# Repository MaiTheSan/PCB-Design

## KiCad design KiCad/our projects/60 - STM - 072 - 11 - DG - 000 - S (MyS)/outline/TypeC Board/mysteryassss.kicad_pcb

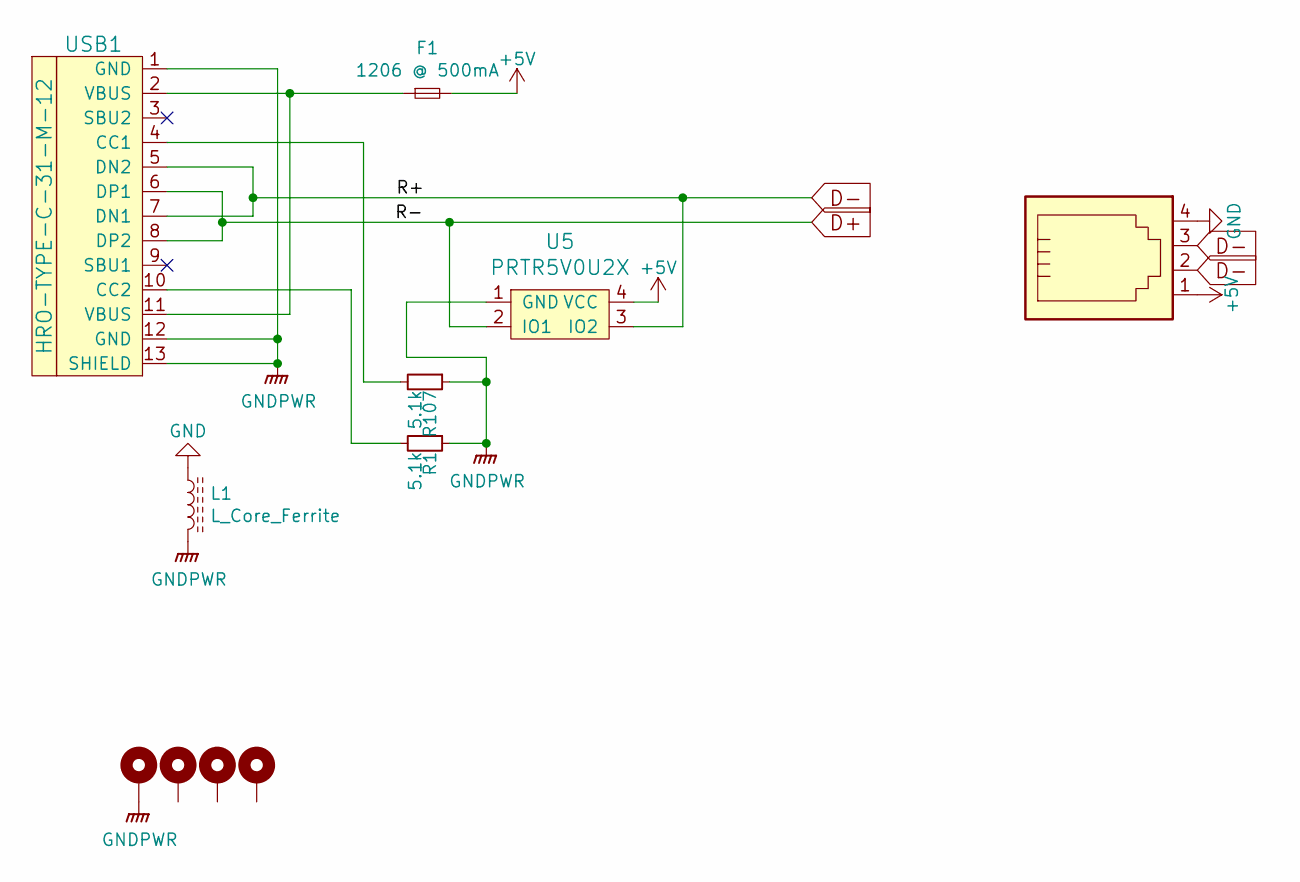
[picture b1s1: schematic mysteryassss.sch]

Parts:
CASE2, CASE3, CASE4, CASE5: ESD inrush; MountingHole_2.2mm_M2_Pad_Via
F1: 1206 @ 500mA; Fuse_1206_3216Metric
J2: 4P4C; JST_SH_SM04B-SRSS-TB_1x04-1MP_P1.00mm_Horizontal
L1: L_Core_Ferrite; L_1206_3216Metric
R1, R107: 5.1k; R_0603
U5: PRTR5V0U2X; SOT143B
USB1: HRO-TYPE-C-31-M-12; HRO-TYPE-C-31-M-12-Assembly

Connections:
+5V: F1.2, J2.1, U5.4 (VCC)
D+: U5.2 (IO1), USB1.6 (DP1), USB1.8 (DP2)
D-: J2.2, J2.3, U5.3 (IO2), USB1.5 (DN2), USB1.7 (DN1)
GND: J2.4, L1.1
GNDPWR: CASE2.1, L1.2, R1.1, R107.1, U5.1 (GND), USB1.1 (GND), USB1.12 (GND), USB1.13 (SHIELD)
unnamed: F1.1, USB1.2 (VBUS), USB1.11 (VBUS)
unnamed: R1.2, USB1.10 (CC2)
unnamed: R107.2, USB1.4 (CC1)

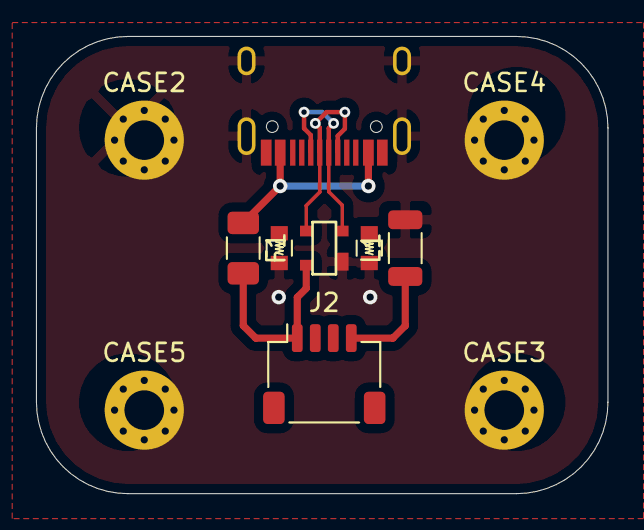
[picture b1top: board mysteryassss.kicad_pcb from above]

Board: 2 copper layers, 31.8 x 25.4 mm, 11 parts (0 on the bottom side), 8 nets.

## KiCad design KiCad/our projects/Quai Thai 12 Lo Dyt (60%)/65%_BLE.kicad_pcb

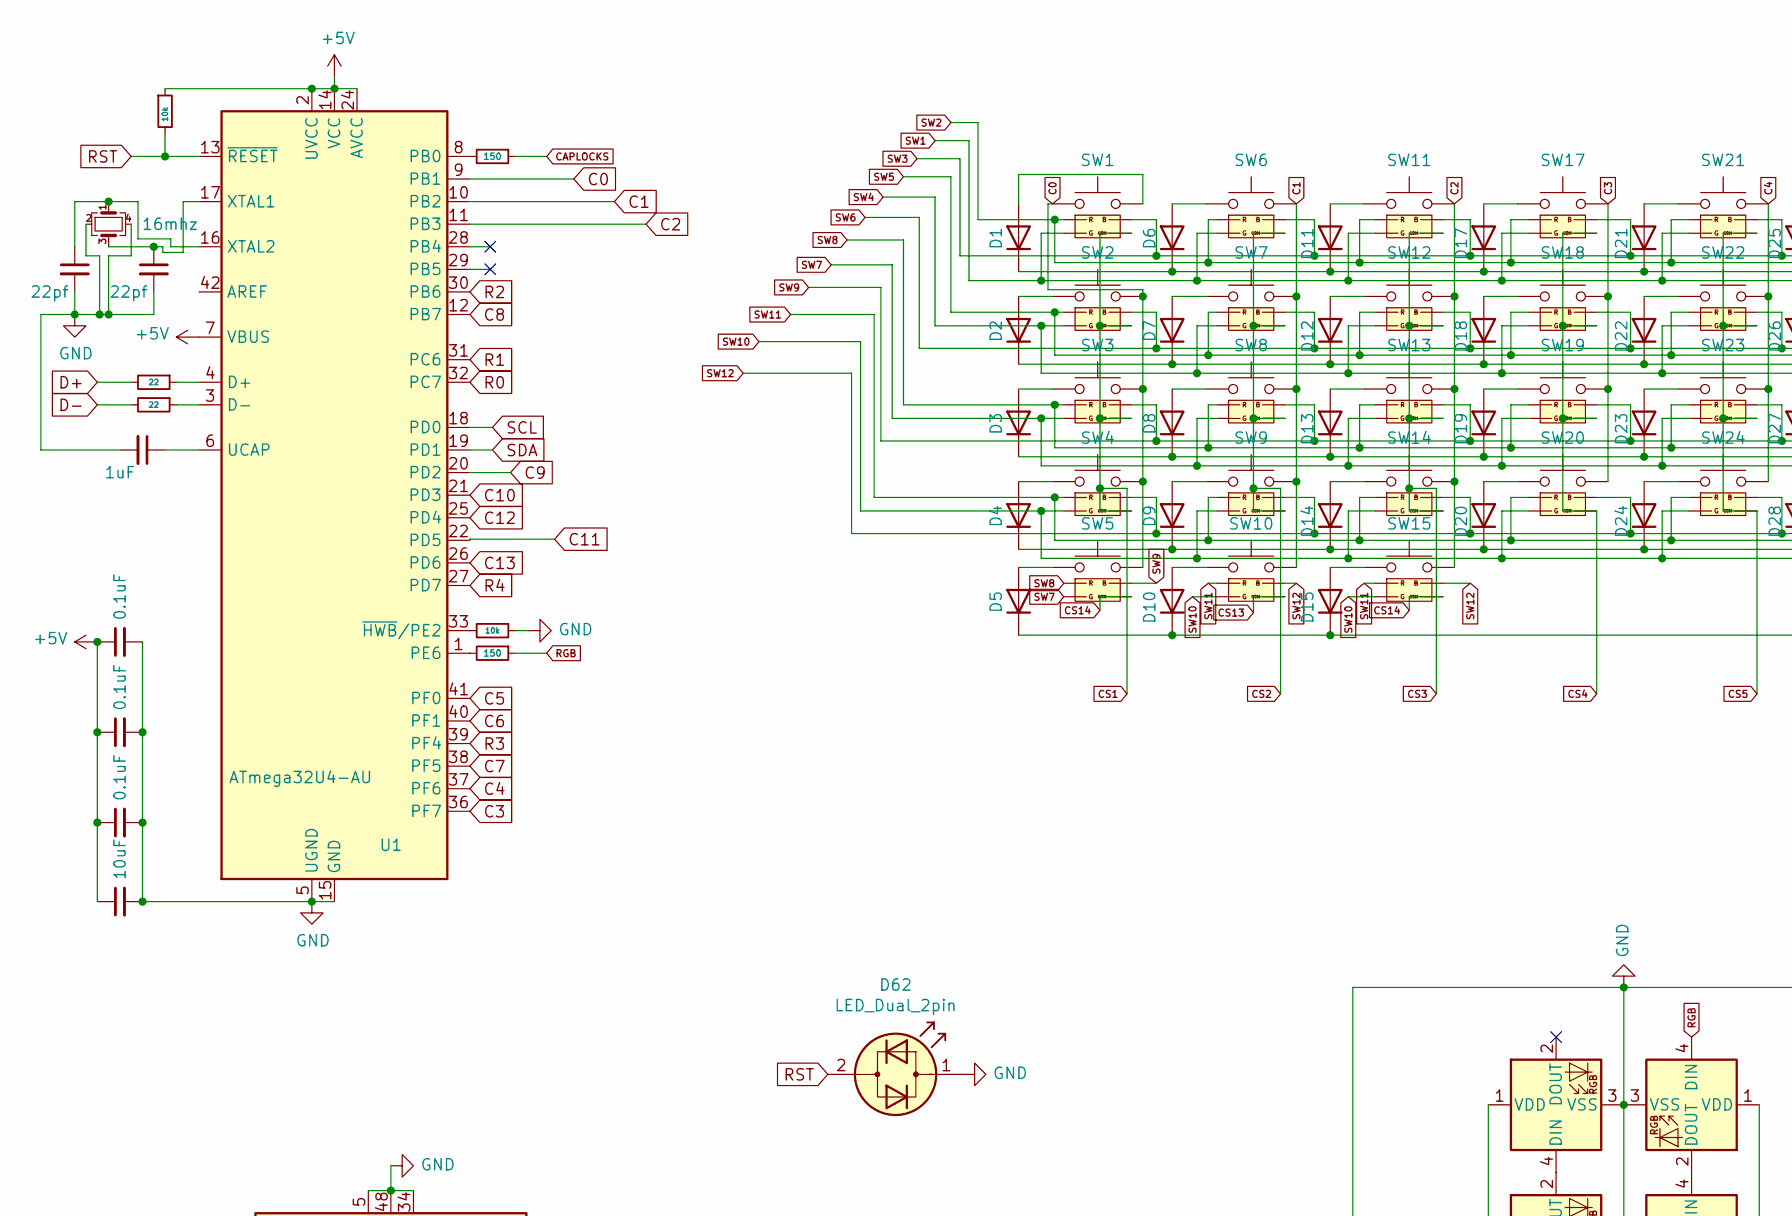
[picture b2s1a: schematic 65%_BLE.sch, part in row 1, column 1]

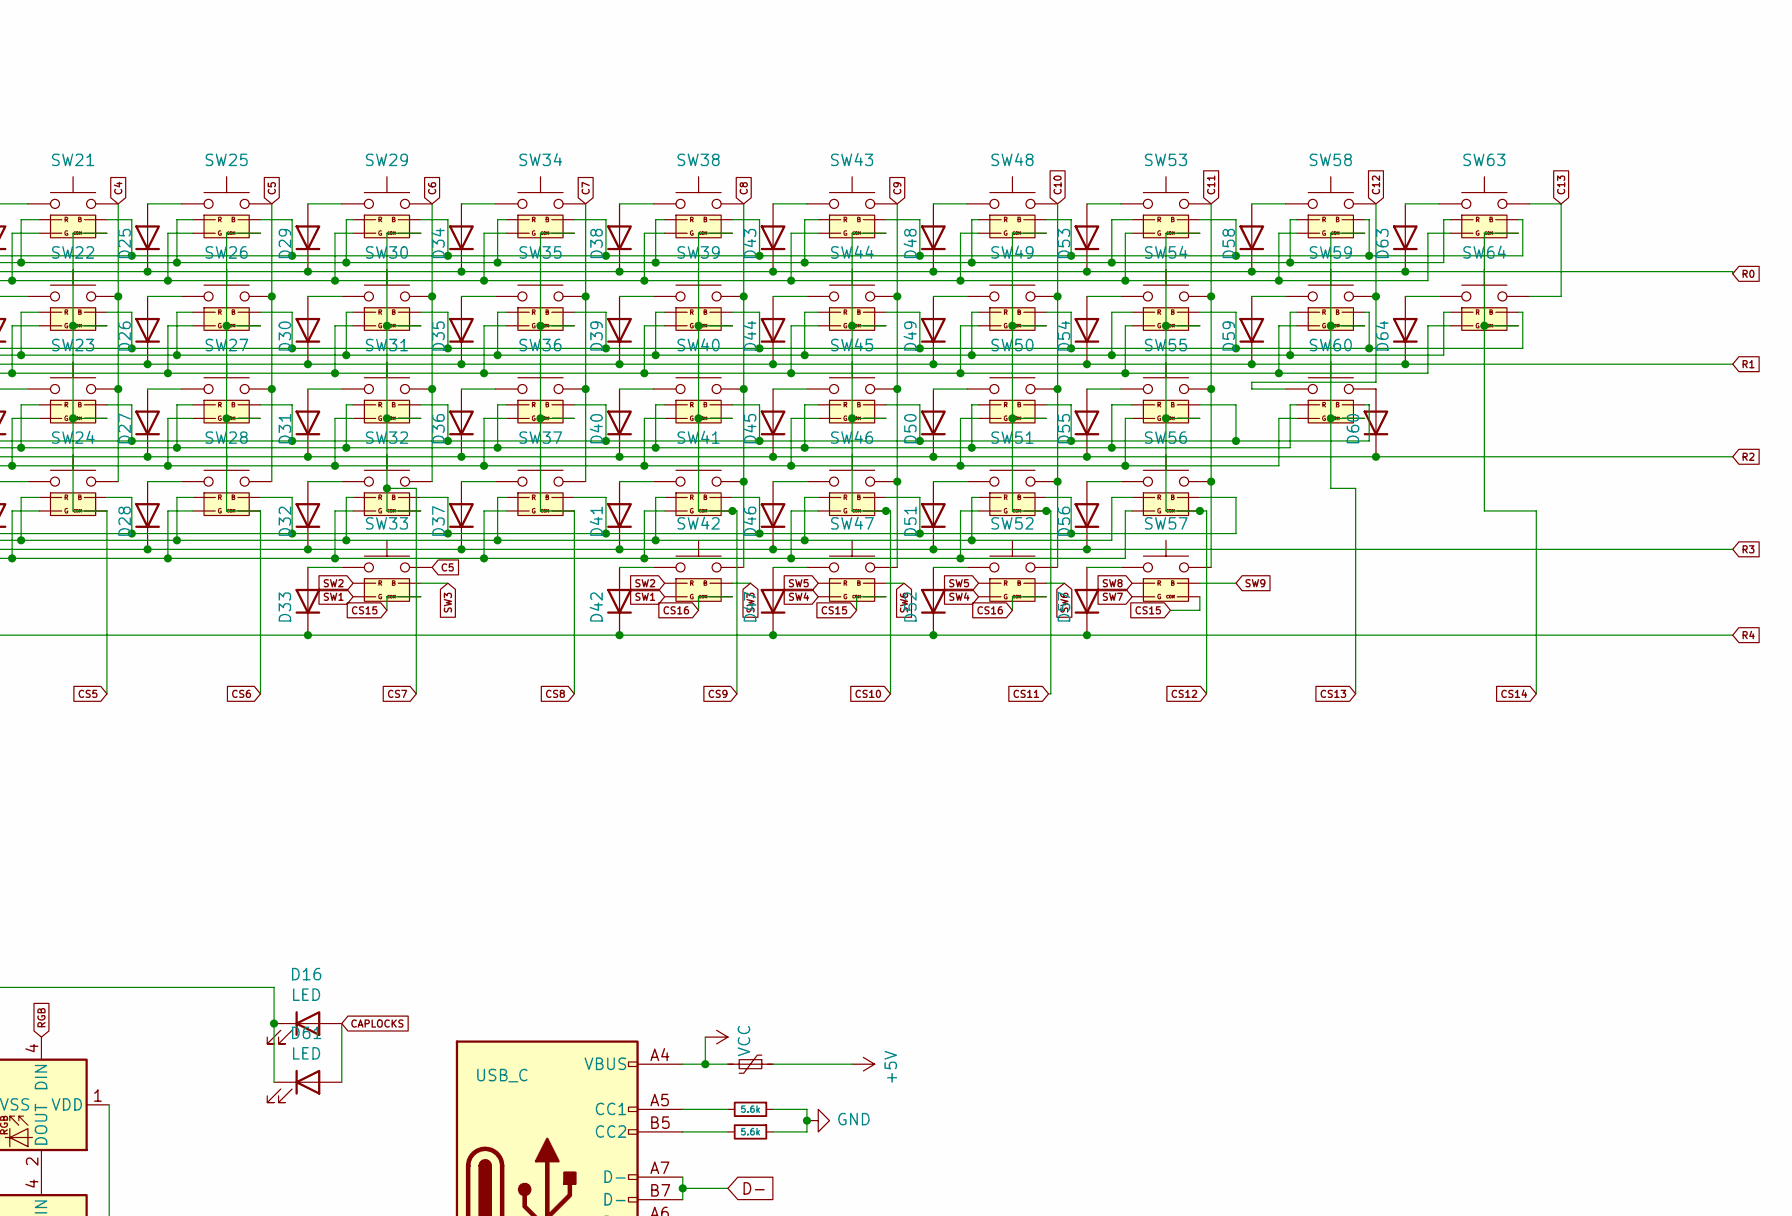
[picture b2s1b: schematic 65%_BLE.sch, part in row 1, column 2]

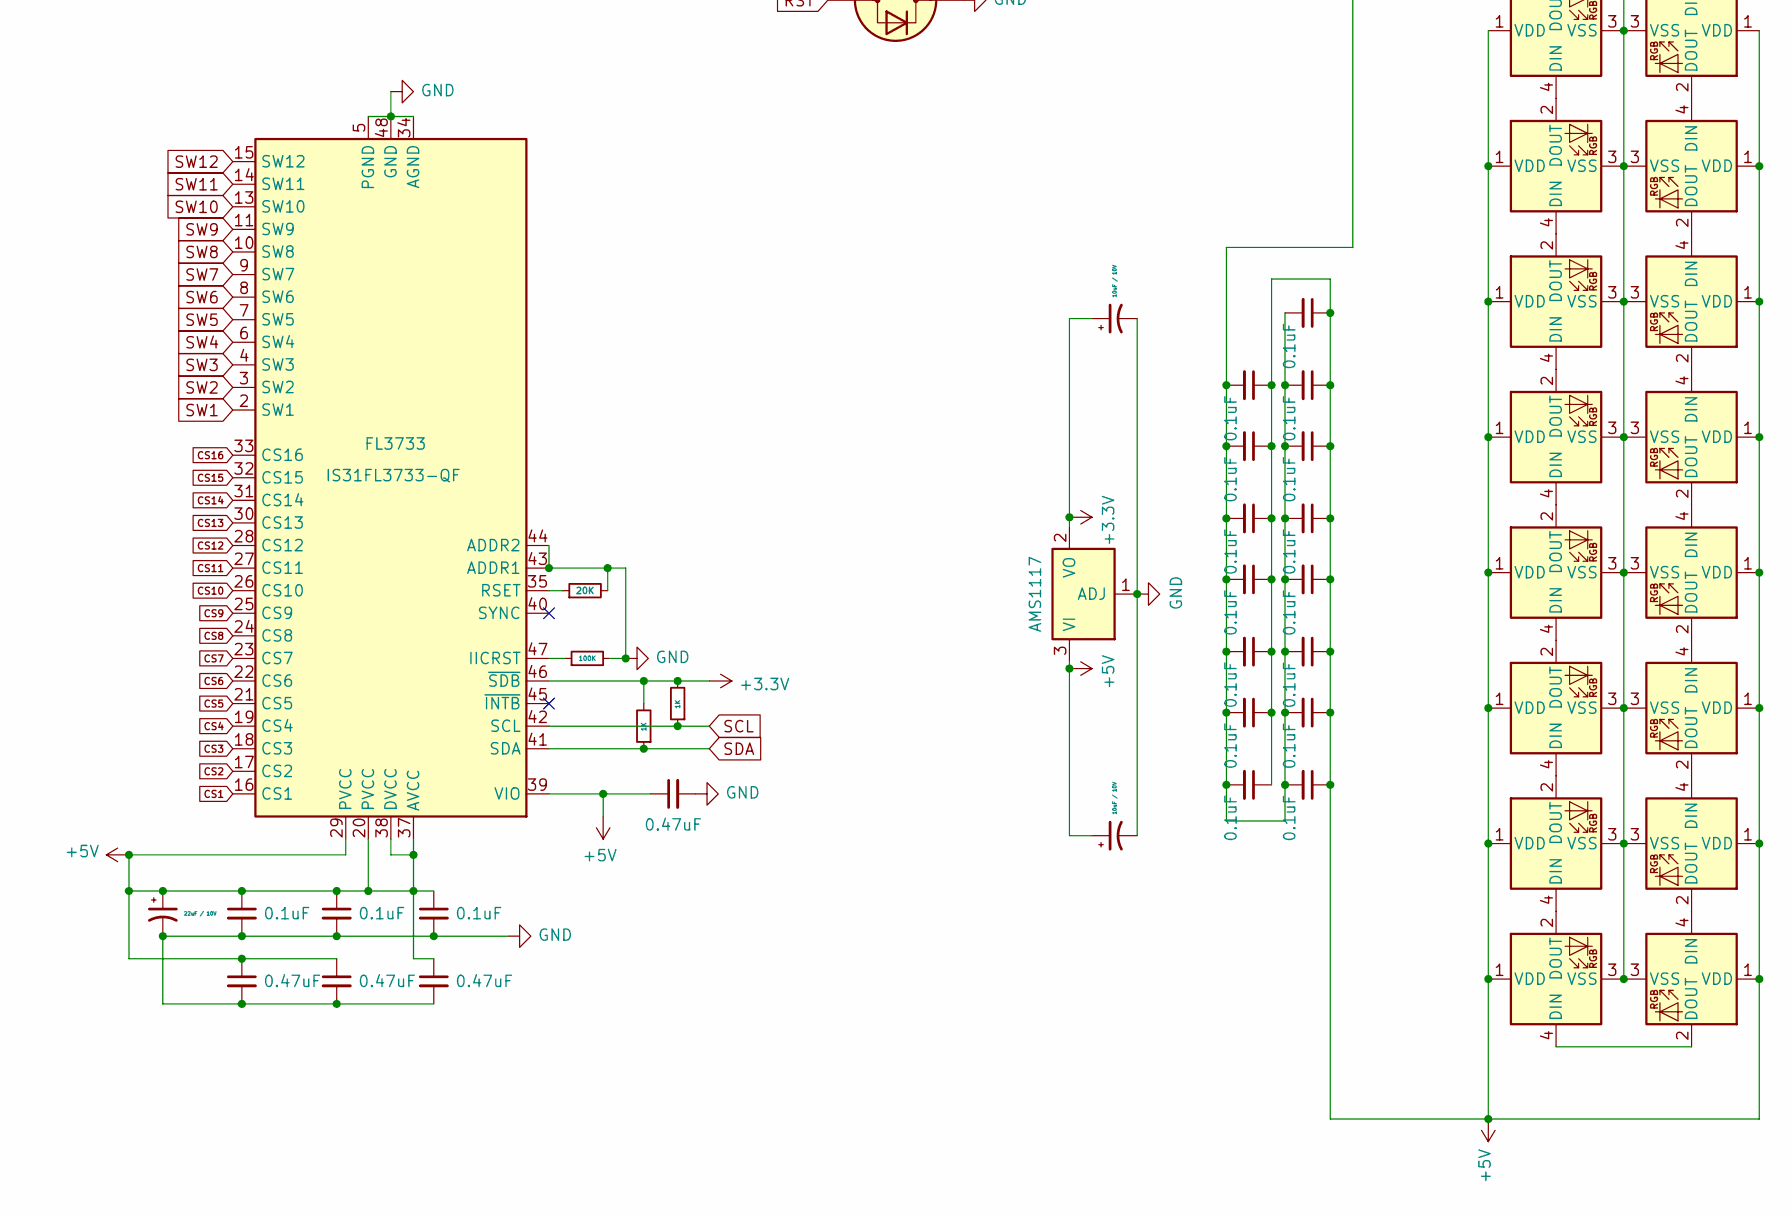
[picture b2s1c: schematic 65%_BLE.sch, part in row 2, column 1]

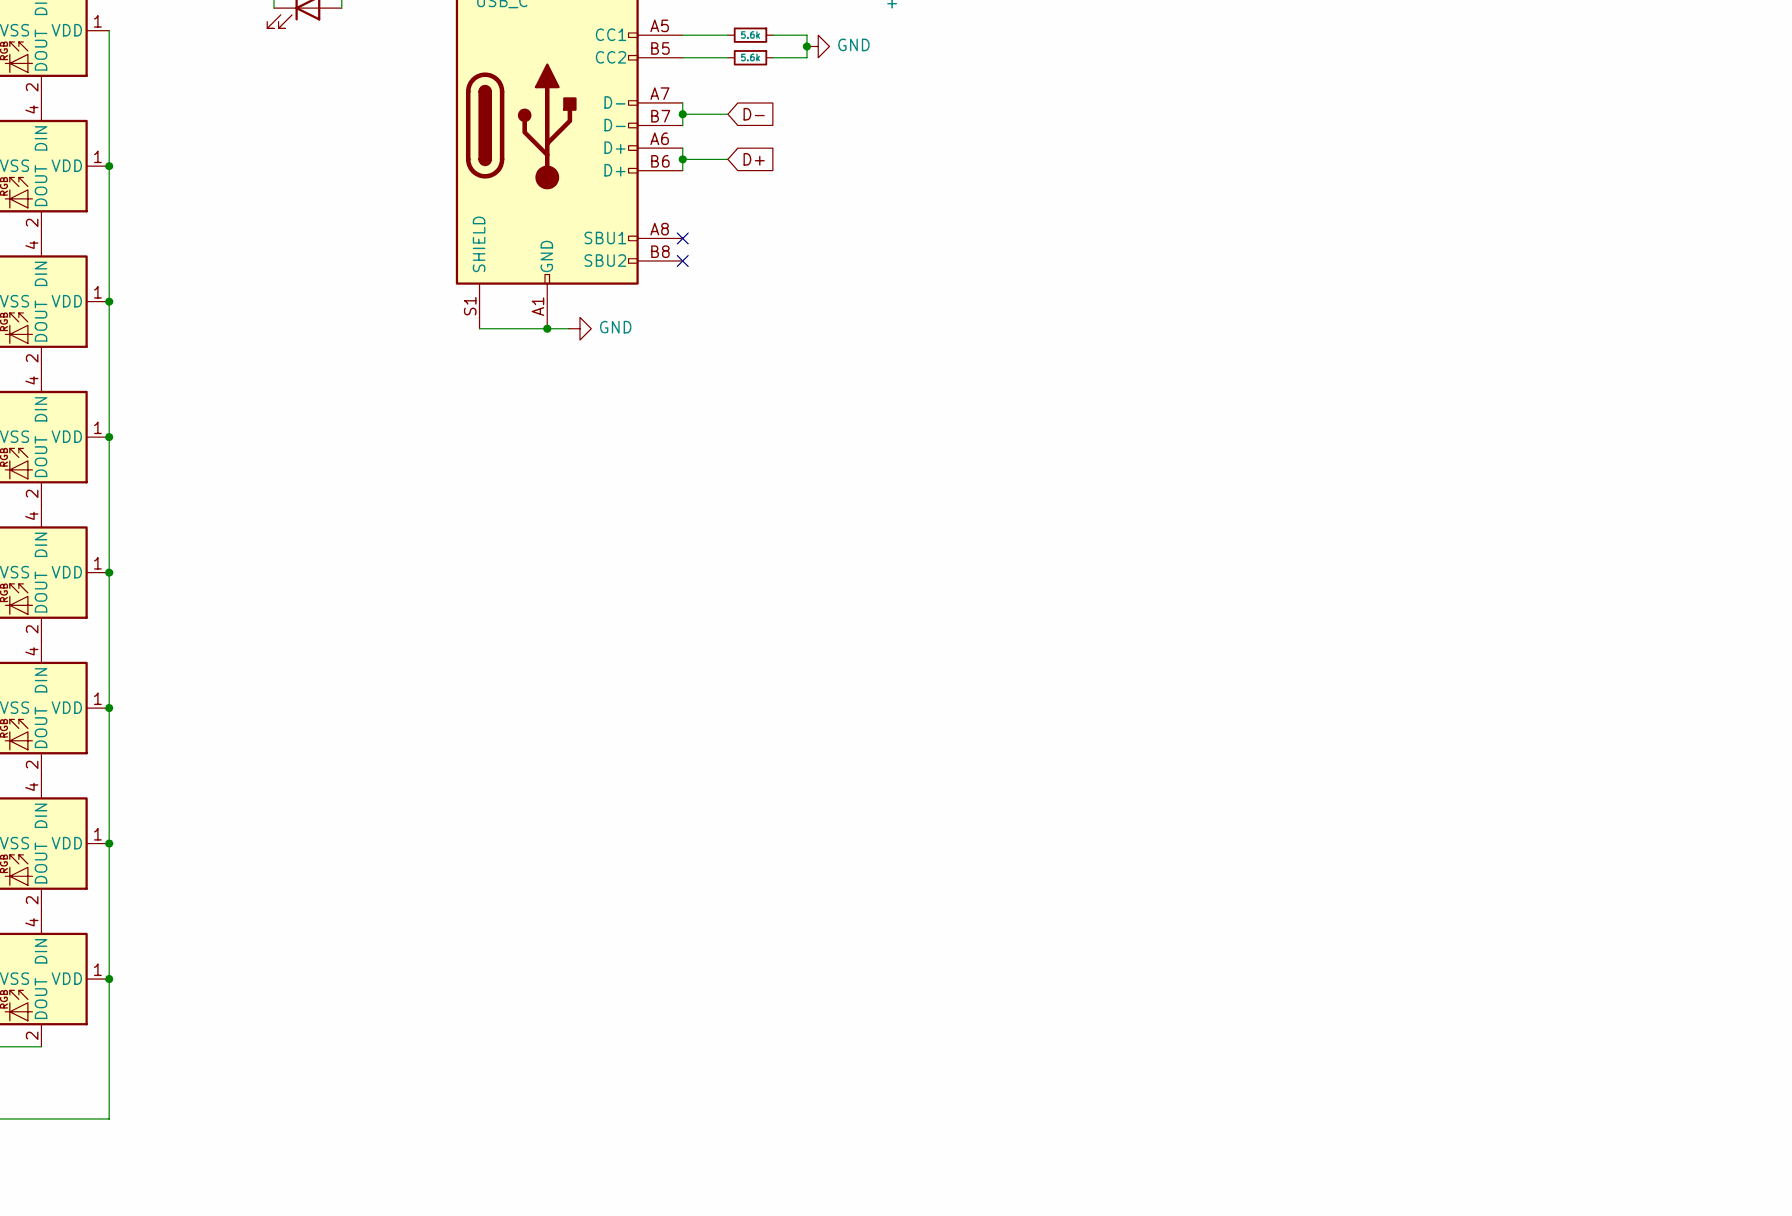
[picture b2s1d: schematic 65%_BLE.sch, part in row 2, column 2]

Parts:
C_1: 10uF; C_0805_2012Metric
C_2, C_3, C_4, C_5, C_6, C_3233: 0.1uF; C_0805_2012Metric
C_3233_1, C_3233_2, C_3233_3: 0.47uF; C_0805_2012Metric
C_ASM1, C_ASM1117: 10uF / 10V; CP_EIA-3528-12_Kemet-T_Pad1.50x2.35mm_HandSolder
C_CAPACITORPOLARISED1: 22uF / 10V; CP_EIA-3528-12_Kemet-T_Pad1.50x2.35mm_HandSolder
C_RGB10, C_RGB11, C_RGB12, C_RGB13, C_RGB14, C_RGB15, C_RGB16, C_RGB17, C_RGB18, C_RGB19, C_RGB20, C_RGB21, C_RGB22, C_RGB23, C_RGB24: 0.1uF; C_0805_2012Metric
C_UCAP1: 1uF; C_0805_2012Metric
C_VIO2: 0.47uF; C_0805_2012Metric
D1, D2, D3, D4, D5, D6, D7, D8, D9, D10, D11, D12, D13, D14, D15, D17, D18, D19, D20, D21, D22, D23, D24, D25, D26, D27, D28, D29, D30, D31, D32, D33, D34, D35, D36, D37, D38, D39, D40, D41, D42, D43, D44, D45, D46, D47, D48, D49, D50, D51, D52, D53, D54, D55, D56, D57, D58, D59, D60, D63, D64: 1N4148; D_SOD-323
D16, D61: LED; LED_PLCC_2835
D62: LED_Dual_2pin; LED_D3.0mm
FL3733: IS31FL3733-QF; QFN-48-1EP_6x6mm_P0.4mm_EP4.2x4.2mm
Fuse1: Polyfuse_Small; Fuse_1812_4532Metric_Castellated
RGB1, RGB10, RGB11, RGB12, RGB13, RGB14, RGB15, RGB16, RGB17, RGB18, RGB19, RGB20, RGB21, RGB22, RGB23, RGB24: WS2812B; LED_WS2812B_PLCC4_5.0x5.0mm_P3.2mm
R_CAPLOCKS1: 150; R_0805_2012Metric
R_CC1, R_CC2: 5.6k; R_0805_2012Metric
R_D+1: 22; R_0805_2012Metric
R_D-1: 22; R_0805_2012Metric
R_HWB1: 10k; R_0805_2012Metric
R_IICRST1: 100K; R_0805_2012Metric
R_RSET1: 20K; R_0805_2012Metric
R_RST1: 10k; R_0805_2012Metric
R_SCL2: 1K; R_0805_2012Metric
R_SDA1: 1K; R_0805_2012Metric
R_rgb1: 150; R_0805_2012Metric
SW1, SW6, SW7, SW8, SW9, SW11, SW12, SW13, SW14, SW17, SW18, SW19, SW20, SW21, SW22, SW23, SW24, SW25, SW26, SW27, SW28, SW29, SW30, SW31, SW32, SW34, SW35, SW36, SW37, SW38, SW39, SW40, SW41, SW43, SW44, SW45, SW46, SW48, SW49, SW50, SW51, SW53, SW54, SW55, SW58, SW59: SW_Push; CherryMX_1.00u_PCB_KailhSocket_LTST-A683CEGBW-HS
SW2, SW64: SW_Push; CherryMX_1.50u_PCB_KailhSocket_LTST-A683CEGBW-HS
SW3: SW_Push; CherryMX_1.75u_PCB_KailhSocket_LTST-A683CEGBW-HS
SW4, SW60: SW_Push; CherryMX_2.25u_PCB_KailhSocket_StabWireTop_LTST-A683CEGBW-HS
SW5, SW10, SW15, SW42, SW47, SW52, SW57: SW_Push; CherryMX_1.25u_PCB_KailhSocket_LTST-A683CEGBW-HS
SW33: SW_Push; CherryMX_6.25u_PCB_KailhSocket_StabWireBottom_LTST-A683CEGB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
SW56: SW_Push; CherryMX_2.75u_PCB_KailhSocket_StabWireTop_LTST-A683CEGBW-HS
SW63: SW_Push; CherryMX_2.00u_PCB_KailhSocket_StabWireTop_LTST-A683CEGBW-HS
TYPE_C1: USB_C; USB_C_Receptacle_Palconn_UTC16-G
U1: ATmega32U4-AU; TQFP-44_10x10mm_P0.8mm
U2: AMS1117; SOT-223-3_TabPin2
Xtal_1, Xtal_2: 22pf; C_0805_2012Metric
crystal1: 16mhz; Crystal_SMD_3225-4Pin_3.2x2.5mm

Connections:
+3V3: C_ASM1117.1, FL3733.46 (~SDB), R_SCL2.2, R_SDA1.2, U2.2 (VO)
+5V: C_1.1, C_2.1, C_3.1, C_4.1, C_5.1, C_6.1, C_3233.1, C_3233_1.1, C_3233_2.1, C_3233_3.1, C_ASM1.1, C_CAPACITORPOLARISED1.1, C_RGB10.1, C_RGB11.1, C_RGB12.1, C_RGB13.1, C_RGB14.1, C_RGB15.1, C_RGB16.1, C_RGB17.1, C_RGB18.1, C_RGB19.1, C_RGB20.1, C_RGB21.1, C_RGB22.1, C_RGB23.1, C_RGB24.1, C_VIO2.1, FL3733.20 (PVCC), FL3733.29 (PVCC), FL3733.37 (AVCC), FL3733.38 (DVCC), FL3733.39 (VIO), Fuse1.1, RGB1.1 (VDD), RGB10.1 (VDD), RGB11.1 (VDD), RGB12.1 (VDD), RGB13.1 (VDD), RGB14.1 (VDD), RGB15.1 (VDD), RGB16.1 (VDD), RGB17.1 (VDD), RGB18.1 (VDD), RGB19.1 (VDD), RGB20.1 (VDD), RGB21.1 (VDD), RGB22.1 (VDD), RGB23.1 (VDD), RGB24.1 (VDD), R_RST1.1, U1.2 (UVCC), U1.7 (VBUS), U1.14 (VCC), U1.24 (AVCC), U1.34 (VCC), U1.44 (AVCC), U2.3 (VI)
C0: SW1.1, SW2.2, SW3.2, SW4.2, SW5.2, U1.9 (PB1)
C1: SW6.2, SW7.2, SW8.2, SW9.2, SW10.2, U1.10 (PB2)
C2: SW11.2, SW12.2, SW13.2, SW14.2, SW15.2, U1.11 (PB3)
C3: SW17.2, SW18.2, SW19.2, SW20.2, U1.36 (PF7)
C4: SW21.2, SW22.2, SW23.2, SW24.2, U1.37 (PF6)
C5: SW25.2, SW26.2, SW27.2, SW28.2, SW33.2, U1.41 (PF0)
C6: SW29.2, SW30.2, SW31.2, SW32.2, U1.40 (PF1)
C7: SW34.2, SW35.2, SW36.2, SW37.2, U1.38 (PF5)
C8: SW38.2, SW39.2, SW40.2, SW41.2, SW42.2, U1.12 (PB7)
C9: SW43.2, SW44.2, SW45.2, SW46.2, SW47.2, U1.20 (PD2)
C10: SW48.2, SW49.2, SW50.2, SW51.2, SW52.2, U1.21 (PD3)
C11: SW53.2, SW54.2, SW55.2, SW56.2, SW57.2, U1.22 (PD5)
C12: SW58.2, SW59.2, SW60.1, U1.25 (PD4)
C13: SW63.2, SW64.2, U1.26 (PD6)
CAPLOCKS: D16.2 (A), D61.2 (A), R_CAPLOCKS1.1
CS1: FL3733.16 (CS1), SW1.3 (A), SW2.3 (A), SW3.3 (A), SW4.3 (A)
CS2: FL3733.17 (CS2), SW6.3 (A), SW7.3 (A), SW8.3 (A), SW9.3 (A)
CS3: FL3733.18 (CS3), SW11.3 (A), SW12.3 (A), SW13.3 (A), SW14.3 (A)
CS4: FL3733.19 (CS4), SW17.3 (A), SW18.3 (A), SW19.3 (A), SW20.3 (A)
CS5: FL3733.21 (CS5), SW21.3 (A), SW22.3 (A), SW23.3 (A), SW24.3 (A)
CS6: FL3733.22 (CS6), SW25.3 (A), SW26.3 (A), SW27.3 (A), SW28.3 (A)
CS7: FL3733.23 (CS7), SW29.3 (A), SW30.3 (A), SW31.3 (A), SW32.3 (A)
CS8: FL3733.24 (CS8), SW34.3 (A), SW35.3 (A), SW36.3 (A), SW37.3 (A)
CS9: FL3733.25 (CS9), SW38.3 (A), SW39.3 (A), SW40.3 (A), SW41.3 (A)
CS10: FL3733.26 (CS10), SW43.3 (A), SW44.3 (A), SW45.3 (A), SW46.3 (A)
CS11: FL3733.27 (CS11), SW48.3 (A), SW49.3 (A), SW50.3 (A), SW51.3 (A)
CS12: FL3733.28 (CS12), SW53.3 (A), SW54.3 (A), SW55.3 (A), SW56.3 (A)
CS13: FL3733.30 (CS13), SW10.3 (A), SW58.3 (A), SW59.3 (A), SW60.3 (A)
CS14: FL3733.31 (CS14), SW5.3 (A), SW15.3 (A), SW63.3 (A), SW64.3 (A)
CS15: FL3733.32 (CS15), SW33.3 (A), SW47.3 (A), SW57.3 (A)
CS16: FL3733.33 (CS16), SW42.3 (A), SW52.3 (A)
D+: R_D-1.2, TYPE_C1.A6 (D+), TYPE_C1.B6 (D+)
D-: R_D+1.2, TYPE_C1.A7 (D-), TYPE_C1.B7 (D-)
GND: C_1.2, C_2.2, C_3.2, C_4.2, C_5.2, C_6.2, C_3233.2, C_3233_1.2, C_3233_2.2, C_3233_3.2, C_ASM1.2, C_ASM1117.2, C_CAPACITORPOLARISED1.2, C_RGB10.2, C_RGB11.2, C_RGB12.2, C_RGB13.2, C_RGB14.2, C_RGB15.2, C_RGB16.2, C_RGB17.2, C_RGB18.2, C_RGB19.2, C_RGB20.2, C_RGB21.2, C_RGB22.2, C_RGB23.2, C_RGB24.2, C_UCAP1.2, C_VIO2.2, D16.1 (K), D61.1 (K), D62.1 (KA), FL3733.5 (PGND), FL3733.12 (PGND), FL3733.34 (AGND), FL3733.43 (ADDR1), FL3733.44 (ADDR2), FL3733.48 (GND), FL3733.49 (GND), RGB1.3 (VSS), RGB10.3 (VSS), RGB11.3 (VSS), RGB12.3 (VSS), RGB13.3 (VSS), RGB14.3 (VSS), RGB15.3 (VSS), RGB16.3 (VSS), RGB17.3 (VSS), RGB18.3 (VSS), RGB19.3 (VSS), RGB20.3 (VSS), RGB21.3 (VSS), RGB22.3 (VSS), RGB23.3 (VSS), RGB24.3 (VSS), R_CC1.1, R_CC2.1, R_HWB1.1, R_IICRST1.2, R_RSET1.2, TYPE_C1.A1 (GND), TYPE_C1.A12 (GND), TYPE_C1.B1 (GND), TYPE_C1.B12 (GND), TYPE_C1.S1 (SHIELD), U1.5 (UGND), U1.15 (GND), U1.23 (GND), U1.35 (GND), U1.43 (GND), U2.1 (ADJ), Xtal_1.2, Xtal_2.2, crystal1.2, crystal1.4
unnamed: C_UCAP1.1, U1.6 (UCAP)
unnamed: D1.2 (A), SW1.2
unnamed: D2.2 (A), SW2.1
unnamed: D3.2 (A), SW3.1
unnamed: D4.2 (A), SW4.1
unnamed: D5.2 (A), SW5.1
unnamed: D6.2 (A), SW6.1
unnamed: D7.2 (A), SW7.1
unnamed: D8.2 (A), SW8.1
unnamed: D9.2 (A), SW9.1
unnamed: D10.2 (A), SW10.1
unnamed: D11.2 (A), SW11.1
unnamed: D12.2 (A), SW12.1
unnamed: D13.2 (A), SW13.1
unnamed: D14.2 (A), SW14.1
unnamed: D15.2 (A), SW15.1
unnamed: D17.2 (A), SW17.1
unnamed: D18.2 (A), SW18.1
unnamed: D19.2 (A), SW19.1
unnamed: D20.2 (A), SW20.1
unnamed: D21.2 (A), SW21.1
unnamed: D22.2 (A), SW22.1
unnamed: D23.2 (A), SW23.1
unnamed: D24.2 (A), SW24.1
unnamed: D25.2 (A), SW25.1
unnamed: D26.2 (A), SW26.1
unnamed: D27.2 (A), SW27.1
unnamed: D28.2 (A), SW28.1
unnamed: D29.2 (A), SW29.1
unnamed: D30.2 (A), SW30.1
unnamed: D31.2 (A), SW31.1
unnamed: D32.2 (A), SW32.1
unnamed: D33.2 (A), SW33.1
unnamed: D34.2 (A), SW34.1
unnamed: D35.2 (A), SW35.1
unnamed: D36.2 (A), SW36.1
unnamed: D37.2 (A), SW37.1
unnamed: D38.2 (A), SW38.1
unnamed: D39.2 (A), SW39.1
unnamed: D40.2 (A), SW40.1
unnamed: D41.2 (A), SW41.1
unnamed: D42.2 (A), SW42.1
unnamed: D43.2 (A), SW43.1
unnamed: D44.2 (A), SW44.1
unnamed: D45.2 (A), SW45.1
unnamed: D46.2 (A), SW46.1
unnamed: D47.2 (A), SW47.1
unnamed: D48.2 (A), SW48.1
unnamed: D49.2 (A), SW49.1
unnamed: D50.2 (A), SW50.1
unnamed: D51.2 (A), SW51.1
unnamed: D52.2 (A), SW52.1
unnamed: D53.2 (A), SW53.1
unnamed: D54.2 (A), SW54.1
unnamed: D55.2 (A), SW55.1
unnamed: D56.2 (A), SW56.1
unnamed: D57.2 (A), SW57.1
unnamed: D58.2 (A), SW58.1
unnamed: D59.2 (A), SW59.1
unnamed: D60.2 (A), SW60.2
unnamed: D63.2 (A), SW63.1
unnamed: D64.2 (A), SW64.1
unnamed: FL3733.35 (RSET), R_RSET1.1
unnamed: FL3733.47 (IICRST), R_IICRST1.1
unnamed: RGB1.4 (DIN), RGB10.2 (DOUT)
unnamed: RGB10.4 (DIN), RGB11.2 (DOUT)
unnamed: RGB11.4 (DIN), RGB12.2 (DOUT)
unnamed: RGB12.4 (DIN), RGB13.2 (DOUT)
unnamed: RGB13.4 (DIN), RGB14.2 (DOUT)
unnamed: RGB14.4 (DIN), RGB15.2 (DOUT)
unnamed: RGB15.4 (DIN), RGB16.2 (DOUT)
unnamed: RGB16.4 (DIN), RGB24.2 (DOUT)
unnamed: RGB17.2 (DOUT), RGB18.4 (DIN)
unnamed: RGB18.2 (DOUT), RGB19.4 (DIN)
unnamed: RGB19.2 (DOUT), RGB20.4 (DIN)
unnamed: RGB20.2 (DOUT), RGB21.4 (DIN)
unnamed: RGB21.2 (DOUT), RGB22.4 (DIN)
unnamed: RGB22.2 (DOUT), RGB23.4 (DIN)
unnamed: RGB23.2 (DOUT), RGB24.4 (DIN)
unnamed: R_CAPLOCKS1.2, U1.8 (PB0)
unnamed: R_CC1.2, TYPE_C1.A5 (CC1)
unnamed: R_CC2.2, TYPE_C1.B5 (CC2)
unnamed: R_D+1.1, U1.3 (D-)
unnamed: R_D-1.1, U1.4 (D+)
unnamed: R_HWB1.2, U1.33 (~HWB~/PE2)
unnamed: R_rgb1.2, U1.1 (PE6)
unnamed: U1.16 (XTAL2), Xtal_2.1, crystal1.1
unnamed: U1.17 (XTAL1), Xtal_1.1, crystal1.3
R0: D1.1 (K), D6.1 (K), D11.1 (K), D17.1 (K), D21.1 (K), D25.1 (K), D29.1 (K), D34.1 (K), D38.1 (K), D43.1 (K), D48.1 (K), D53.1 (K), D58.1 (K), D63.1 (K), U1.32 (PC7)
R1: D2.1 (K), D7.1 (K), D12.1 (K), D18.1 (K), D22.1 (K), D26.1 (K), D30.1 (K), D35.1 (K), D39.1 (K), D44.1 (K), D49.1 (K), D54.1 (K), D59.1 (K), D64.1 (K), U1.31 (PC6)
R2: D3.1 (K), D8.1 (K), D13.1 (K), D19.1 (K), D23.1 (K), D27.1 (K), D31.1 (K), D36.1 (K), D40.1 (K), D45.1 (K), D50.1 (K), D55.1 (K), D60.1 (K), U1.30 (PB6)
R3: D4.1 (K), D9.1 (K), D14.1 (K), D20.1 (K), D24.1 (K), D28.1 (K), D32.1 (K), D37.1 (K), D41.1 (K), D46.1 (K), D51.1 (K), D56.1 (K), U1.39 (PF4)
R4: D5.1 (K), D10.1 (K), D15.1 (K), D33.1 (K), D42.1 (K), D47.1 (K), D52.1 (K), D57.1 (K), U1.27 (PD7)
RGB: RGB17.4 (DIN), R_rgb1.1
RST: D62.2 (AK), R_RST1.2, U1.13 (~RESET)
SCL: FL3733.42 (SCL), R_SCL2.1, U1.18 (PD0)
SDA: FL3733.41 (SDA), R_SDA1.1, U1.19 (PD1)
SW1: FL3733.2 (SW1), SW1.4 (GK), SW6.4 (GK), SW11.4 (GK), SW17.4 (GK), SW21.4 (GK), SW25.4 (GK), SW29.4 (GK), SW33.4 (GK), SW34.4 (GK), SW38.4 (GK), SW42.4 (GK), SW43.4 (GK), SW48.4 (GK), SW53.4 (GK), SW58.4 (GK), SW63.4 (GK)
SW2: FL3733.3 (SW2), SW1.5 (RK), SW6.5 (RK), SW11.5 (RK), SW17.5 (RK), SW21.5 (RK), SW25.5 (RK), SW29.5 (RK), SW33.5 (RK), SW34.5 (RK), SW38.5 (RK), SW42.5 (RK), SW43.5 (RK), SW48.5 (RK), SW53.5 (RK), SW58.5 (RK), SW63.5 (RK)
SW3: FL3733.4 (SW3), SW1.6 (BK), SW6.6 (BK), SW11.6 (BK), SW17.6 (BK), SW21.6 (BK), SW25.6 (BK), SW29.6 (BK), SW33.6 (BK), SW34.6 (BK), SW38.6 (BK), SW42.6 (BK), SW43.6 (BK), SW48.6 (BK), SW53.6 (BK), SW58.6 (BK), SW63.6 (BK)
SW4: FL3733.6 (SW4), SW2.4 (GK), SW7.4 (GK), SW12.4 (GK), SW18.4 (GK), SW22.4 (GK), SW26.4 (GK), SW30.4 (GK), SW35.4 (GK), SW39.4 (GK), SW44.4 (GK), SW47.4 (GK), SW49.4 (GK), SW52.4 (GK), SW54.4 (GK), SW59.4 (GK), SW64.4 (GK)
SW5: FL3733.7 (SW5), SW2.5 (RK), SW7.5 (RK), SW12.5 (RK), SW18.5 (RK), SW22.5 (RK), SW26.5 (RK), SW30.5 (RK), SW35.5 (RK), SW39.5 (RK), SW44.5 (RK), SW47.5 (RK), SW49.5 (RK), SW52.5 (RK), SW54.5 (RK), SW59.5 (RK), SW64.5 (RK)
SW6: FL3733.8 (SW6), SW2.6 (BK), SW7.6 (BK), SW12.6 (BK), SW18.6 (BK), SW22.6 (BK), SW26.6 (BK), SW30.6 (BK), SW35.6 (BK), SW39.6 (BK), SW44.6 (BK), SW47.6 (BK), SW49.6 (BK), SW52.6 (BK), SW54.6 (BK), SW59.6 (BK), SW64.6 (BK)
SW7: FL3733.9 (SW7), SW3.4 (GK), SW5.4 (GK), SW8.4 (GK), SW13.4 (GK), SW19.4 (GK), SW23.4 (GK), SW27.4 (GK), SW31.4 (GK), SW36.4 (GK), SW40.4 (GK), SW45.4 (GK), SW50.4 (GK), SW55.4 (GK), SW57.4 (GK), SW60.4 (GK)
SW8: FL3733.10 (SW8), SW3.5 (RK), SW5.5 (RK), SW8.5 (RK), SW13.5 (RK), SW19.5 (RK), SW23.5 (RK), SW27.5 (RK), SW31.5 (RK), SW36.5 (RK), SW40.5 (RK), SW45.5 (RK), SW50.5 (RK), SW55.5 (RK), SW57.5 (RK), SW60.5 (RK)
SW9: FL3733.11 (SW9), SW3.6 (BK), SW5.6 (BK), SW8.6 (BK), SW13.6 (BK), SW19.6 (BK), SW23.6 (BK), SW27.6 (BK), SW31.6 (BK), SW36.6 (BK), SW40.6 (BK), SW45.6 (BK), SW50.6 (BK), SW55.6 (BK), SW57.6 (BK), SW60.6 (BK)
SW10: FL3733.13 (SW10), SW4.4 (GK), SW9.4 (GK), SW10.4 (GK), SW14.4 (GK), SW15.4 (GK), SW20.4 (GK), SW24.4 (GK), SW28.4 (GK), SW32.4 (GK), SW37.4 (GK), SW41.4 (GK), SW46.4 (GK), SW51.4 (GK), SW56.4 (GK)
SW11: FL3733.14 (SW11), SW4.5 (RK), SW9.5 (RK), SW10.5 (RK), SW14.5 (RK), SW15.5 (RK), SW20.5 (RK), SW24.5 (RK), SW28.5 (RK), SW32.5 (RK), SW37.5 (RK), SW41.5 (RK), SW46.5 (RK), SW51.5 (RK), SW56.5 (RK)
SW12: FL3733.15 (SW12), SW4.6 (BK), SW9.6 (BK), SW10.6 (BK), SW14.6 (BK), SW15.6 (BK), SW20.6 (BK), SW24.6 (BK), SW28.6 (BK), SW32.6 (BK), SW37.6 (BK), SW41.6 (BK), SW46.6 (BK), SW51.6 (BK), SW56.6 (BK)
VCC: Fuse1.2, TYPE_C1.A4 (VBUS), TYPE_C1.A9 (VBUS), TYPE_C1.B4 (VBUS), TYPE_C1.B9 (VBUS)

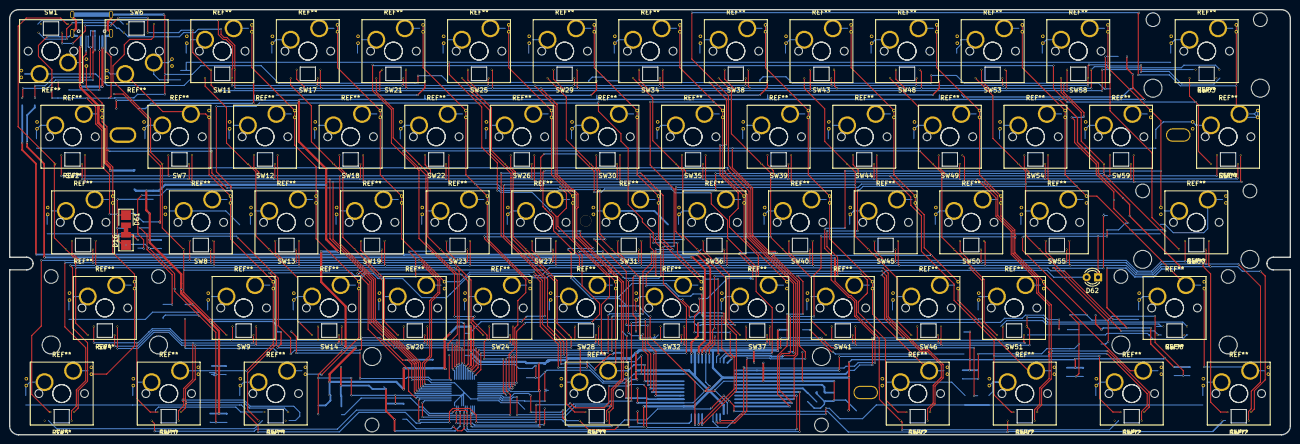
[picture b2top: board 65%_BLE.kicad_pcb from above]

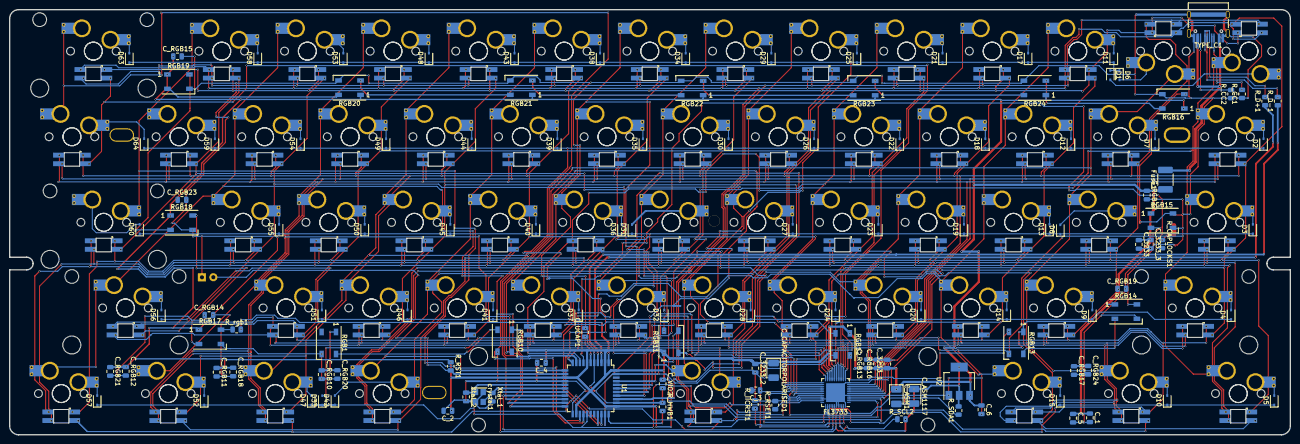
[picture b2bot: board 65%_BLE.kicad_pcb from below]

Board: 2 copper layers, 285.0 x 94.6 mm, 191 parts (127 on the bottom side), 146 nets.
